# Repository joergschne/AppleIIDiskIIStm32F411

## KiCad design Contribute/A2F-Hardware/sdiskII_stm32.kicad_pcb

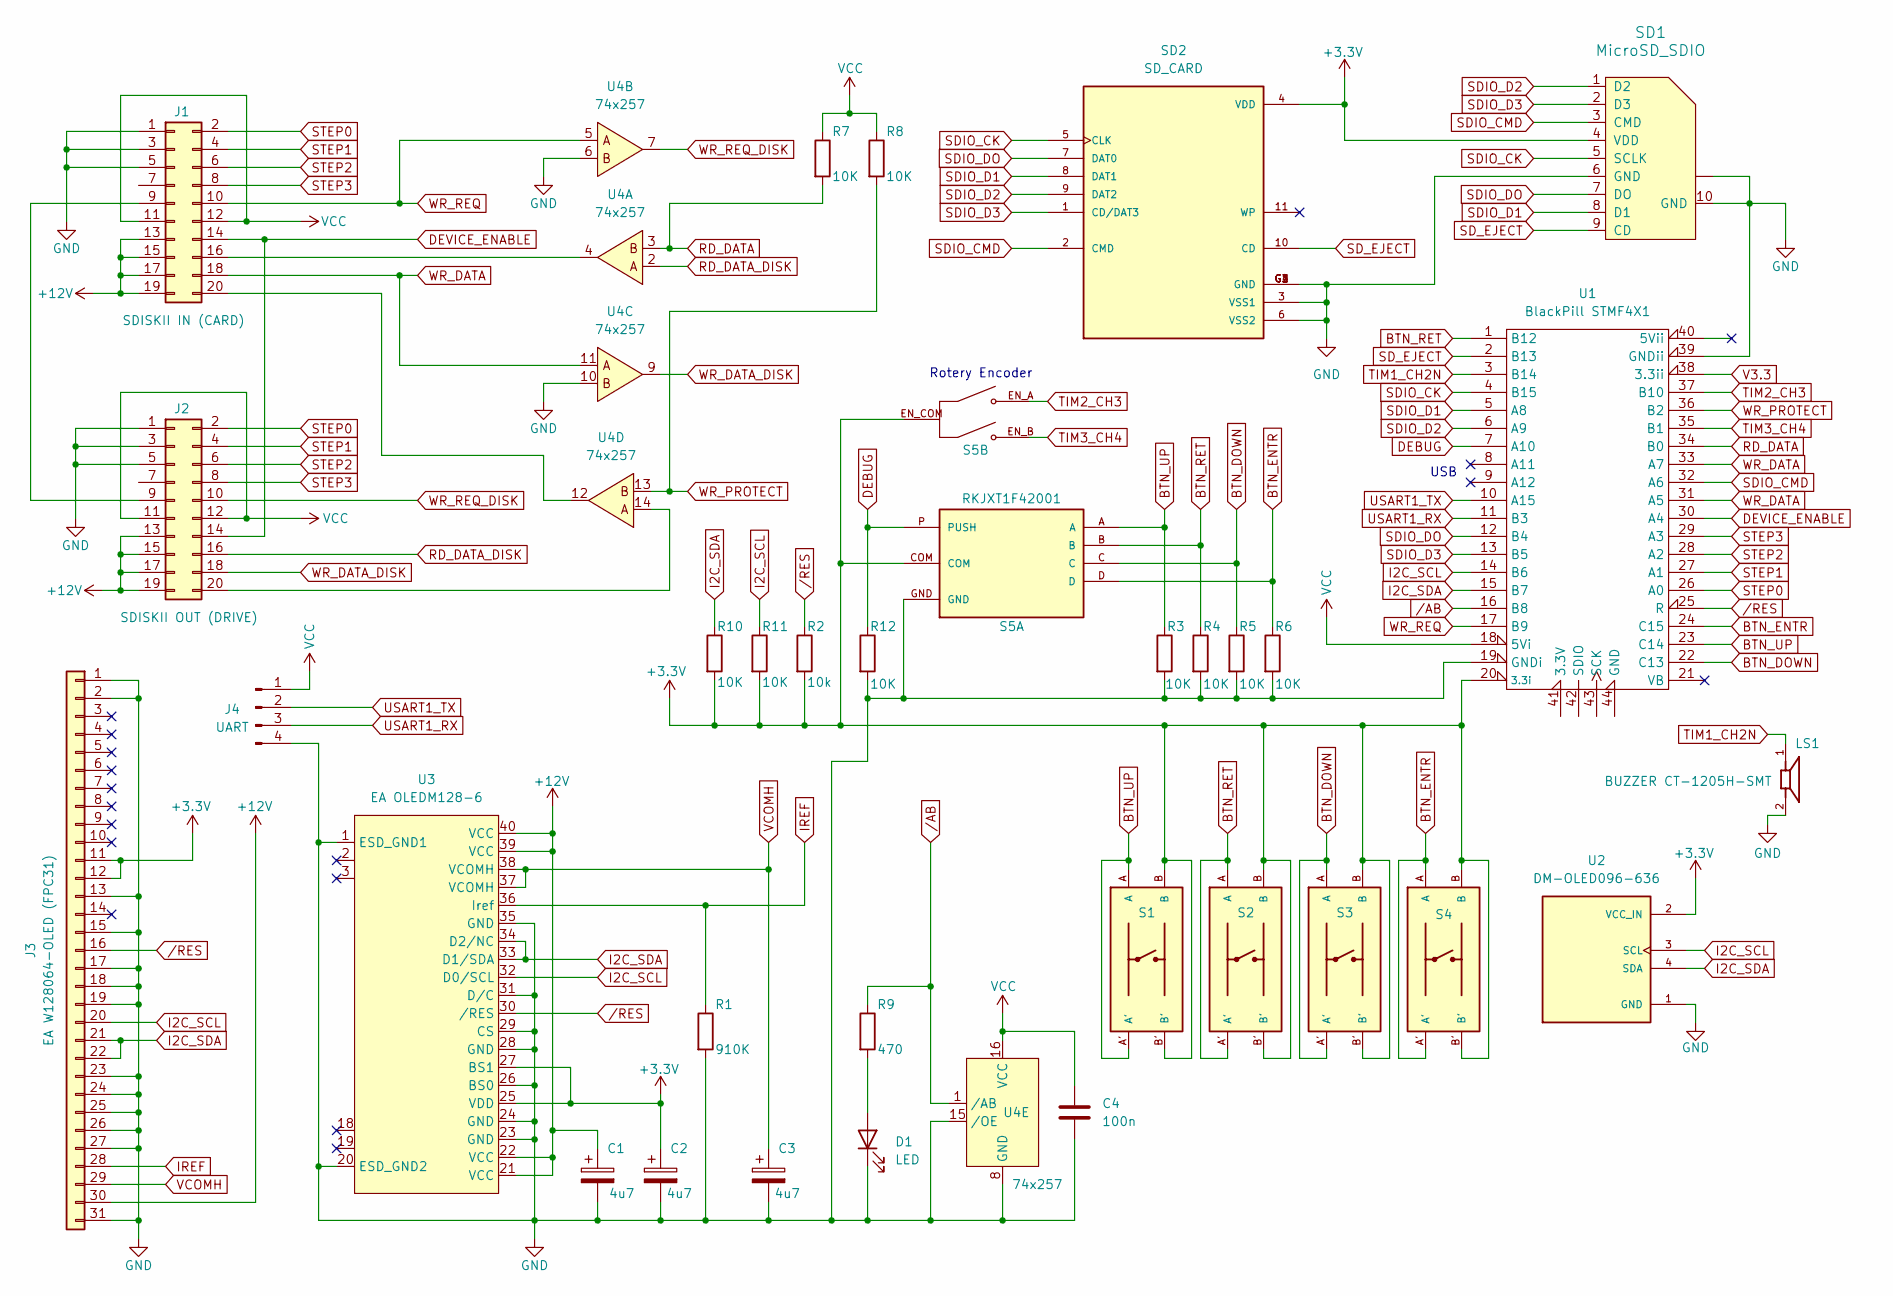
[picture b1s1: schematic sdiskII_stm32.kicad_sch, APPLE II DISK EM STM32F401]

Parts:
C1, C2, C3: 4u7; CP_EIA-3216-18_Kemet-A_Pad1.58x1.35mm_HandSolder
C4: 100n; C_0805_2012Metric_Pad1.18x1.45mm_HandSolder
D1: LED; LED_D3.0mm
J1: SDISKII IN (CARD); IDC-Header_2x10_P2.54mm_Vertical
J2: SDISKII OUT (DRIVE); IDC-Header_2x10_P2.54mm_Vertical
J3: EA W128064-OLED (FPC31); AMPHENOL_F32R-1A7H1-11031
J4: UART; PinHeader_1x04_P2.54mm_Vertical
LS1: BUZZER CT-1205H-SMT; BUZZER CUI_CT-1205H-SMT; PART_REV 1.02
R1: 910K; R_0805_2012Metric_Pad1.20x1.40mm_HandSolder
R2: 10k; R_0805_2012Metric_Pad1.20x1.40mm_HandSolder
R3, R4, R5, R6, R7, R8, R10, R11, R12: 10K; R_0805_2012Metric_Pad1.20x1.40mm_HandSolder
R9: 470; R_0805_2012Metric_Pad1.20x1.40mm_HandSolder
S1, S2, S3, S4: EVQ-Q2B02W; SW_EVQ-Q2B02W
S5: RKJXT1F42001; ALPS XDCR_RKJXT1F42001
SD1: MicroSD_SDIO; GCT-MEM2055-00-190-01-A_VIB
SD2: SD_CARD; SD_CARD_AMPHENOL_GMC020080HR; PARTREV AX6
U1: BlackPill STMF4X1; Mini_F4X1_STM32_VIB
U2: DM-OLED096-636; MODULE_DM-OLED096-636-SMAL; PARTREV 2018-09-10
U3: EA OLEDM128-6
U4: 74x257; SOIC-16_3.9x9.9mm_P1.27mm

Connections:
+3.3V: C2.1, J3.11, J3.12, R2.2, R10.2, R11.2, S1.B, S1.B', S2.B, S2.B', S3.B, S3.B', S4.B, S4.B', S5.COM, S5.EN_COM, SD1.4 (VDD), SD2.4 (VDD), U1.20 (3.3i), U2.2 (VCC_IN), U3.25 (VDD), U3.27 (BS1)
+12V: C1.1, J1.13, J1.15, J1.17, J1.19, J2.13, J2.15, J2.17, J2.19, J3.30, U3.21 (VCC), U3.22 (VCC), U3.39 (VCC), U3.40 (VCC)
BTN_DOWN: R5.1, S3.A, S3.A', S5.C, U1.22 (C13)
BTN_ENTR: R6.1, S4.A, S4.A', S5.D, U1.24 (C15)
BTN_RET: R4.1, S2.A, S2.A', S5.B, U1.1 (B12)
BTN_UP: R3.1, S1.A, S1.A', S5.A, U1.23 (C14)
DEBUG: R12.1, S5.P (PUSH), U1.7 (A10)
DEVICE_ENABLE: J1.14, J2.14, U1.30 (A4)
GND: C1.2, C2.2, C3.2, C4.2, D1.1 (K), J1.1, J1.3, J1.5, J1.7, J2.1, J2.3, J2.5, J2.7, J3.1, J3.2, J3.13, J3.15, J3.17, J3.18, J3.19, J3.23, J3.24, J3.25, J3.26, J3.27, J3.31, J4.4, LS1.2, R1.2, R3.2, R4.2, R5.2, R6.2, R12.2, S5.GND, SD1.6 (GND), SD1.10 (GND), SD1.~, SD2.3 (VSS1), SD2.6 (VSS2), SD2.G1 (GND), SD2.G2 (GND), SD2.G3 (GND), SD2.G4 (GND), U1.19 (GNDi), U1.39 (GNDii), U2.1 (GND), U3.1 (ESD_GND1), U3.20 (ESD_GND2), U3.23 (GND), U3.24 (GND), U3.26 (BS0), U3.28 (GND), U3.29 (CS), U3.31 (D/C), U3.35 (GND), U4.6, U4.8 (GND), U4.10, U4.15 (/OE)
I2C_SCL: J3.20, R11.1, U1.14 (B6), U2.3 (SCL), U3.32 (D0/SCL)
I2C_SDA: J3.21, J3.22, R10.1, U1.15 (B7), U2.4 (SDA), U3.33 (D1/SDA), U3.34 (D2/NC)
IREF: J3.28, R1.1, U3.36 (Iref)
unnamed: D1.2 (A), R9.2
unnamed: J1.9, J2.9
unnamed: J1.16, U4.4
unnamed: J1.20, U4.12
unnamed: J2.20, U4.14
RD_DATA: R7.2, U1.34 (B0), U4.3
RD_DATA_DISK: J2.16, U4.2
SDIO_CK: SD1.5 (SCLK), SD2.5 (CLK), U1.4 (B15)
SDIO_CMD: SD1.3 (CMD), SD2.2 (CMD), U1.32 (A6)
SDIO_D1: SD1.8 (D1), SD2.8 (DAT1), U1.5 (A8)
SDIO_D2: SD1.1 (D2), SD2.9 (DAT2), U1.6 (A9)
SDIO_D3: SD1.2 (D3), SD2.1 (CD/DAT3), U1.13 (B5)
SDIO_DO: SD1.7 (DO), SD2.7 (DAT0), U1.12 (B4)
SD_EJECT: SD1.9 (CD), SD2.10 (CD), U1.2 (B13)
STEP0: J1.2, J2.2, U1.26 (A0)
STEP1: J1.4, J2.4, U1.27 (A1)
STEP2: J1.6, J2.6, U1.28 (A2)
STEP3: J1.8, J2.8, U1.29 (A3)
TIM1_CH2N: LS1.1, U1.3 (B14)
TIM2_CH3: S5.EN_A, U1.37 (B10)
TIM3_CH4: S5.EN_B, U1.35 (B1)
USART1_RX: J4.3, U1.11 (B3)
USART1_TX: J4.2, U1.10 (A15)
V3.3: U1.38 (3.3ii)
VCC: C4.1, J1.11, J1.12, J2.11, J2.12, J4.1, R7.1, R8.1, U1.18 (5Vi), U4.16 (VCC)
VCOMH: C3.1, J3.29, U3.37 (VCOMH), U3.38 (VCOMH)
WR_DATA: J1.18, U1.31 (A5), U1.33 (A7), U4.11
WR_DATA_DISK: J2.18, U4.9
WR_PROTECT: R8.2, U1.36 (B2), U4.13
WR_REQ: J1.10, U1.17 (B9), U4.5
WR_REQ_DISK: J2.10, U4.7
/AB: R9.1, U1.16 (B8), U4.1 (/AB)
/RES: J3.16, R2.1, U1.25 (R), U3.30 (/RES)

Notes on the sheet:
USB
Rotery Encoder

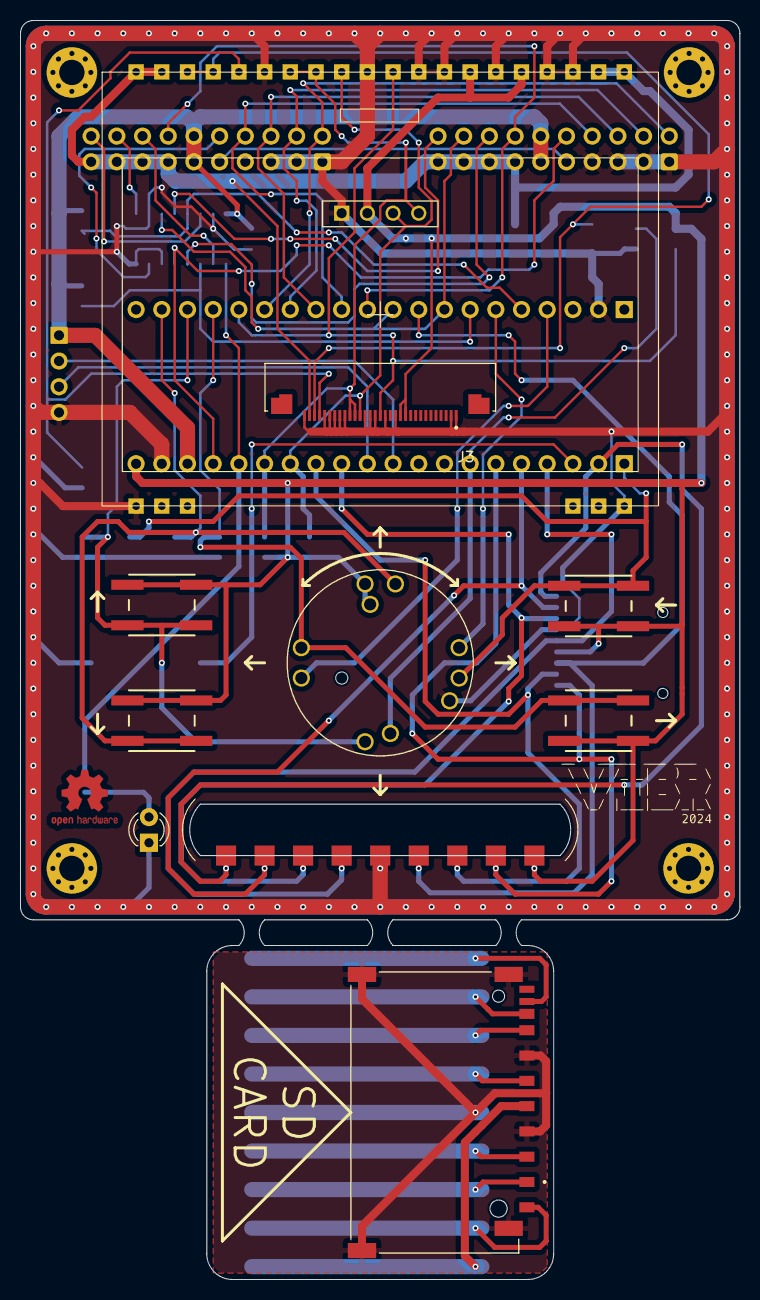
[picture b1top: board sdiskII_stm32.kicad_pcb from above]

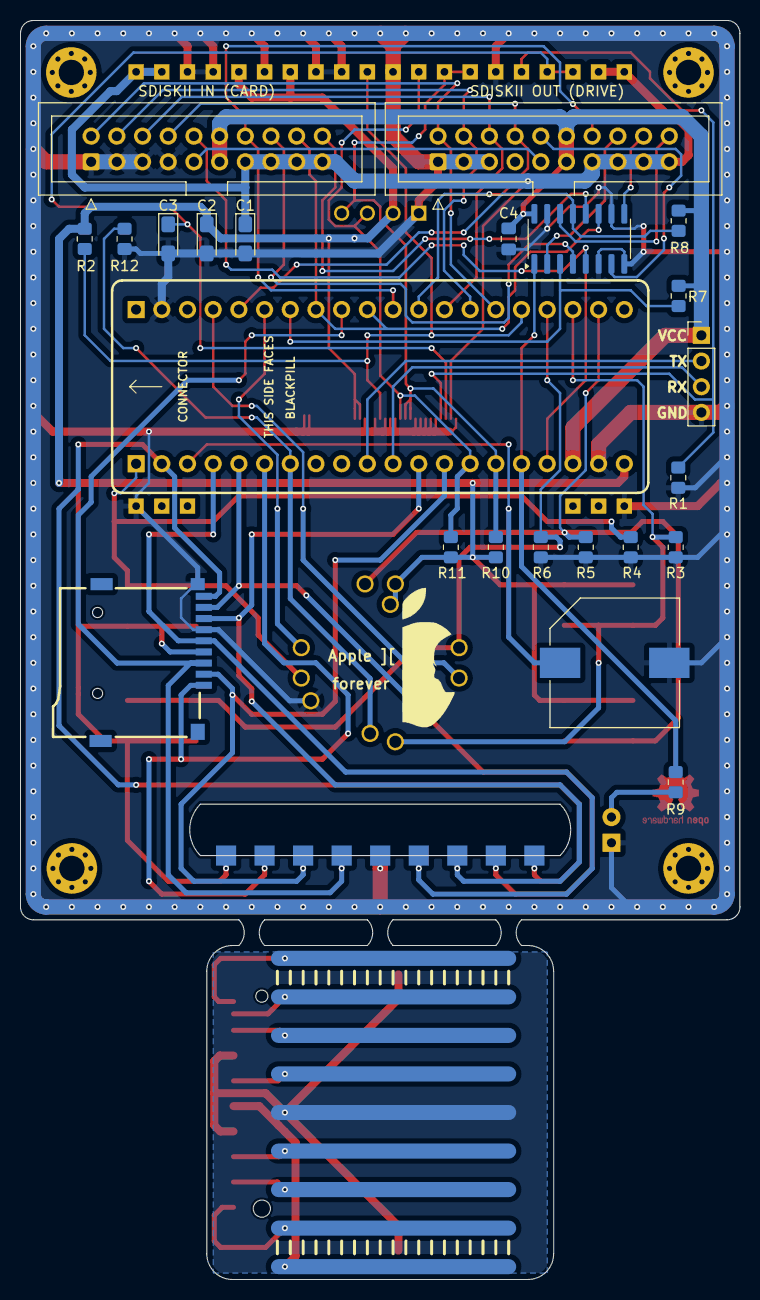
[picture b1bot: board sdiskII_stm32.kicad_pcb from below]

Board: 2 copper layers, 71.1 x 124.5 mm, 38 parts (23 on the bottom side), 44 nets.

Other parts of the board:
H1, H2, H3, H4: MountingHole_2.5mm_Pad_Via
VIBR: LOGO

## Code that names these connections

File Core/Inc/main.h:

/* USER CODE BEGIN Header */
/**
  ******************************************************************************
  * @file           : main.h
  * @brief          : Header for main.c file.
  *                   This file contains the common defines of the application.
  ******************************************************************************
  * @attention
  *
  * Copyright (c) 2024 STMicroelectronics.
  * All rights reserved.
  *
  * This software is licensed under terms that can be found in the LICENSE file
  * in the root directory of this software component.
  * If no LICENSE file comes with this software, it is provided AS-IS.
  *
  ******************************************************************************
  */
/* USER CODE END Header */

/* Define to prevent recursive inclusion -------------------------------------*/
#ifndef __MAIN_H
#define __MAIN_H

#ifdef __cplusplus
extern "C" {
#endif

/* Includes ------------------------------------------------------------------*/
#include "stm32f4xx_hal.h"

/* Private includes ----------------------------------------------------------*/
/* USER CODE BEGIN Includes */
#include "list.h"
#include "defines.h"



/* USER CODE END Includes */

/* Exported types ------------------------------------------------------------*/
/* USER CODE BEGIN ET */

/* USER CODE END ET */

/* Exported constants --------------------------------------------------------*/
/* USER CODE BEGIN EC */

/* USER CODE END EC */

/* Exported macro ------------------------------------------------------------*/
/* USER CODE BEGIN EM */
#ifdef __GNUC__
#define PUTCHAR_PROTOTYPE int __io_putchar(int ch)
#else
#define PUTCHAR_PROTOTYPE int fputc(int ch, FILE *f)
#endif
/* USER CODE END EM */

void HAL_TIM_MspPostInit(TIM_HandleTypeDef *htim);

/* Exported functions prototypes ---------------------------------------------*/
void Error_Handler(void);

/* USER CODE BEGIN EFP */
enum action{NONE,IMG_MOUNT,FSDISP,FSMOUNT,SYSRESET,DUMP_TX,WRITE_TRK,UPDIMGDISP,PROCESS_FS_CHANGEDIR};

enum FS_STATUS{READY,READING,WRITING,BUSY,DBG};
enum EMULATION_TYPE{DISKII,  SMARTPORTHD,DISK35 };

enum STATUS{RET_OK,RET_ERR};

void EnableTiming(void);
void dumpBuf(unsigned char * buf,long memoryAddr,int len);
enum STATUS dumpBufFile(char * filename,volatile unsigned char * buffer,int length);
enum STATUS writeTrkFile(char * filename,char * buffer,uint32_t offset);

char *byte_to_binary(int x);

list_t * sortLinkedList(list_t * plst);                             // Sort the chainedList
enum STATUS walkDir(char * path);                                   // Build chainedList of Directories/Files Items

enum STATUS mountImagefile(char * filename);
enum STATUS unmountImage();
enum STATUS unlinkImageFile(char* fullpathfilename);

void processBtnInterrupt(uint16_t GPIO_Pin);



void debounceBtn(int GPIO);

void irqReadTrack();
void irqWriteTrack();
void irqWIdle();

void irqEnableSDIO();
void irqDisableSDIO();

void Custom_SD_WriteCpltCallback(void);
void Custom_SD_ReadCpltCallback(void);

void getDataBlocksBareMetal(long memoryAdr,volatile unsigned char * buffer,int count);
void setDataBlocksBareMetal(long memoryAdr,volatile unsigned char * buffer,int count);

void processDiskHeadMoveInterrupt(uint16_t GPIO_Pin);
char processDeviceEnableInterrupt(uint16_t GPIO_Pin);
char processSdEject(uint16_t GPIO_PIN);

enum STATUS makeSDFS();

enum STATUS mountImagefile(char * filename);
enum STATUS initeBeaming();

typedef struct image_info_s {
  char title[32];
  uint8_t favorite;
  uint8_t type;
  uint8_t version;
  uint8_t writeProtected;
  uint8_t synced;
  uint8_t cleaned;
  uint8_t optimalBitTiming;
} image_info_t;


/* USER CODE END EFP */

/* Private defines -----------------------------------------------------------*/
#define BTN_DOWN_Pin GPIO_PIN_13
#define BTN_DOWN_GPIO_Port GPIOC
#define BTN_DOWN_EXTI_IRQn EXTI15_10_IRQn
#define BTN_UP_Pin GPIO_PIN_14
#define BTN_UP_GPIO_Port GPIOC
#define BTN_UP_EXTI_IRQn EXTI15_10_IRQn
#define BTN_ENTR_Pin GPIO_PIN_15
#define BTN_ENTR_GPIO_Port GPIOC
#define BTN_ENTR_EXTI_IRQn EXTI15_10_IRQn
#define STEP0_Pin GPIO_PIN_0
#define STEP0_GPIO_Port GPIOA
#define STEP0_EXTI_IRQn EXTI0_IRQn
#define STEP1_Pin GPIO_PIN_1
#define STEP1_GPIO_Port GPIOA
#define STEP1_EXTI_IRQn EXTI1_IRQn
#define STEP2_Pin GPIO_PIN_2
#define STEP2_GPIO_Port GPIOA
#define STEP2_EXTI_IRQn EXTI2_IRQn
#define STEP3_Pin GPIO_PIN_3
#define STEP3_GPIO_Port GPIOA
#define STEP3_EXTI_IRQn EXTI3_IRQn
#define DEVICE_ENABLE_Pin GPIO_PIN_4
#define DEVICE_ENABLE_GPIO_Port GPIOA
#define DEVICE_ENABLE_EXTI_IRQn EXTI4_IRQn
#define WR_DATA_Pin GPIO_PIN_7
#define WR_DATA_GPIO_Port GPIOA
#define RD_DATA_Pin GPIO_PIN_0
#define RD_DATA_GPIO_Port GPIOB
#define WR_PROTECT_Pin GPIO_PIN_2
#define WR_PROTECT_GPIO_Port GPIOB
#define BTN_RET_Pin GPIO_PIN_12
#define BTN_RET_GPIO_Port GPIOB
#define BTN_RET_EXTI_IRQn EXTI15_10_IRQn
#define SD_EJECT_Pin GPIO_PIN_13
#define SD_EJECT_GPIO_Port GPIOB
#define DEBUG_Pin GPIO_PIN_10
#define DEBUG_GPIO_Port GPIOA
#define WR_REQ_Pin GPIO_PIN_9
#define WR_REQ_GPIO_Port GPIOB
#define WR_REQ_EXTI_IRQn EXTI9_5_IRQn
#ifdef A2F_MODE
#define AB_Pin GPIO_PIN_8
#define AB_GPIO_Port GPIOB
#define ENCODER_A_Pin GPIO_PIN_1
#define ENCODER_A_GPIO_Port GPIOB
#define ENCODER_B_Pin GPIO_PIN_10
#define ENCODER_B_GPIO_Port GPIOB
#endif
/* USER CODE BEGIN Private defines */

/* USER CODE END Private defines */

#ifdef __cplusplus
}
#endif

#endif /* __MAIN_H */

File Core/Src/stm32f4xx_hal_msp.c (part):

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    __HAL_RCC_GPIOA_CLK_ENABLE();
    __HAL_RCC_GPIOB_CLK_ENABLE();
    /**SDIO GPIO Configuration
    PA6     ------> SDIO_CMD
    PB15     ------> SDIO_CK
    PA8     ------> SDIO_D1
    PA9     ------> SDIO_D2
    PB4     ------> SDIO_D0
    PB5     ------> SDIO_D3
    */
    GPIO_InitStruct.Pin = GPIO_PIN_6|GPIO_PIN_8|GPIO_PIN_9;
    GPIO_InitStruct.Mode = GPIO_MODE_AF_PP;
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    __HAL_RCC_SDIO_CLK_DISABLE();

    /**SDIO GPIO Configuration
    PA6     ------> SDIO_CMD
    PB15     ------> SDIO_CK
    PA8     ------> SDIO_D1
    PA9     ------> SDIO_D2
    PB4     ------> SDIO_D0
    PB5     ------> SDIO_D3
    */
    HAL_GPIO_DeInit(GPIOA, GPIO_PIN_6|GPIO_PIN_8|GPIO_PIN_9);

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  /* USER CODE END TIM1_MspPostInit 0 */
    __HAL_RCC_GPIOB_CLK_ENABLE();
    /**TIM1 GPIO Configuration
    PB14     ------> TIM1_CH2N
    */
    GPIO_InitStruct.Pin = GPIO_PIN_14;
    GPIO_InitStruct.Mode = GPIO_MODE_AF_PP;
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
    __HAL_RCC_GPIOB_CLK_ENABLE();
    /**TIM2 GPIO Configuration
    PB10     ------> TIM2_CH3
    */
    GPIO_InitStruct.Pin = GPIO_PIN_10;
    GPIO_InitStruct.Mode = GPIO_MODE_AF_PP;
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
    __HAL_RCC_GPIOB_CLK_ENABLE();
    /**TIM3 GPIO Configuration
    PB1     ------> TIM3_CH4
    */
    GPIO_InitStruct.Pin = GPIO_PIN_1;
    GPIO_InitStruct.Mode = GPIO_MODE_AF_PP;
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
    /**TIM2 GPIO Configuration
    PA5     ------> TIM2_ETR
    PB10     ------> TIM2_CH3
    */
    HAL_GPIO_DeInit(GPIOA, GPIO_PIN_5);

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    __HAL_RCC_GPIOA_CLK_ENABLE();
    __HAL_RCC_GPIOB_CLK_ENABLE();
    /**USART1 GPIO Configuration
    PA15     ------> USART1_TX
    PB3     ------> USART1_RX
    */
    GPIO_InitStruct.Pin = GPIO_PIN_15;
    GPIO_InitStruct.Mode = GPIO_MODE_AF_PP;
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    __HAL_RCC_USART1_CLK_DISABLE();

    /**USART1 GPIO Configuration
    PA15     ------> USART1_TX
    PB3     ------> USART1_RX
    */
    HAL_GPIO_DeInit(GPIOA, GPIO_PIN_15);

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
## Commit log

2024-12-25 initial A2F mode
